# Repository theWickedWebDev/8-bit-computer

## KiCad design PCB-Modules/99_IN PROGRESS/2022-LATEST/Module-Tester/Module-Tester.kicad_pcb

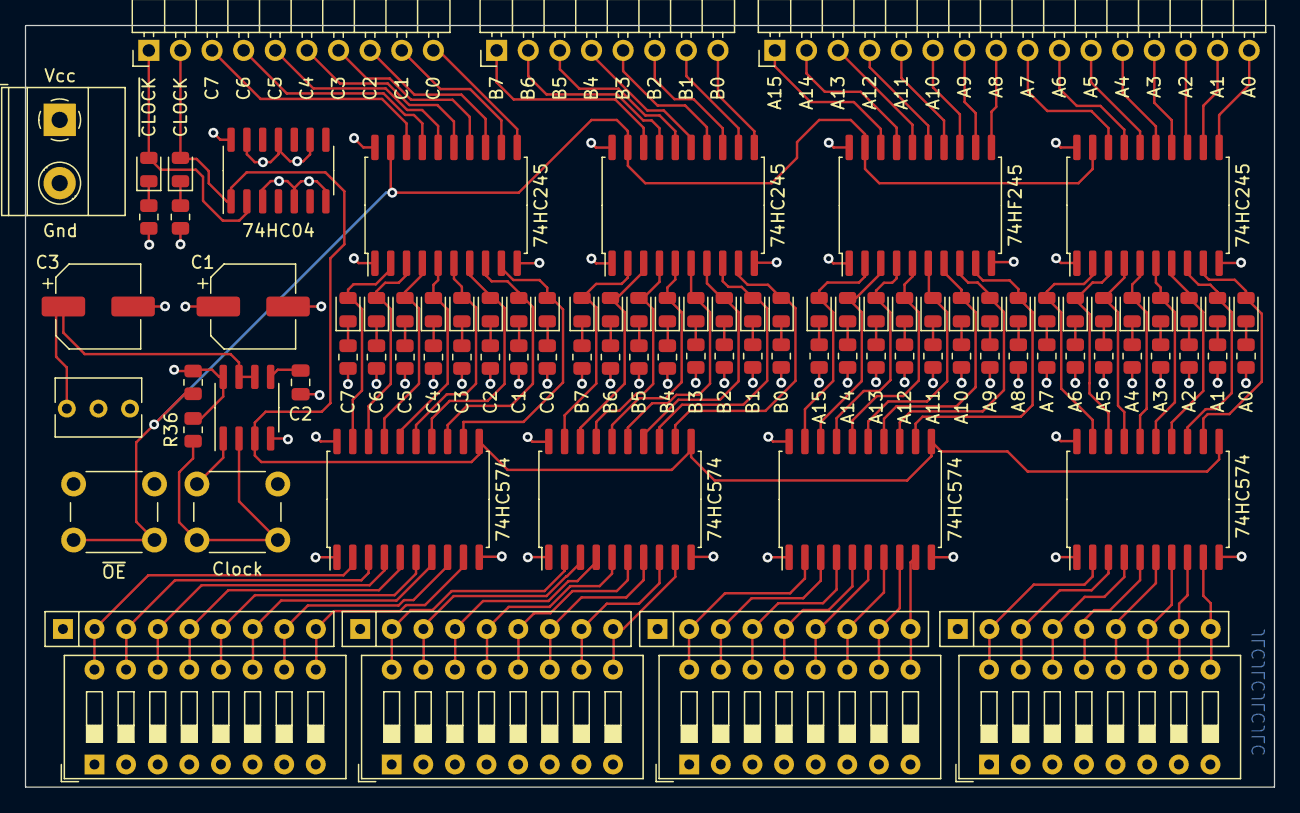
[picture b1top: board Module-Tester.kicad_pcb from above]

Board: 4 copper layers, 100.3 x 61.2 mm, 98 parts (0 on the bottom side), 138 nets.

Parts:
C1, C3: CS1V220M-CRE54; CP_Elec_6.3x5.4
C2: 0402B102K500NT; C_0805_2012Metric
D1, D2, D3, D4, D5, D6, D7, D8, D9, D10, D11, D12, D13, D14, D15, D16, D17, D18, D19, D20, D21, D22, D23, D24, D25, D26, D27, D28, D29, D30, D31, D32, D33, D34: LED; LED_0805_2012Metric
J1: Screw_Terminal_01x02; TerminalBlock_Phoenix_MKDS-1,5-2-5.08_1x02_P5.08mm_Horizont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
J2: Conn_01x10; PinHeader_1x10_P2.54mm_Horizontal
J3: Conn_01x08; PinHeader_1x08_P2.54mm_Horizontal
J4: Conn_01x16; PinHeader_1x16_P2.54mm_Horizontal
R1, R2, R3, R4, R5, R6, R7, R8, R9, R10, R11, R12, R13, R14, R15, R16, R17, R18, R19, R20, R21, R22, R23, R24, R25, R26, R27, R28, R29, R30, R31, R32, R33, R34: R_Small_US; R_0805_2012Metric
R35, R36: 0402WGF1002TCE; R_0805_2012Metric
RN1, RN2, RN3, RN4: R_Network08; R_Array_SIP9
RV1: 3296W-1-203; Potentiometer_Bourns_3266Y_Vertical
SW1, SW2, SW3, SW4: SW_DIP_x08; SW_DIP_SPSTx08_Slide_9.78x22.5mm_W7.62mm_P2.54mm
SW5: SW_SPST; SW_PUSH_6mm
SW6: sw-push; SW_PUSH_6mm
U1, U2, U5, U6: 74LS574; SOIC-20W_7.5x12.8mm_P1.27mm
U3, U4, U7, U8: 74LS245; SOIC-20W_7.5x12.8mm_P1.27mm
U9: LMC555CMX/NOPB; SOIC-8_3.9x4.9mm_P1.27mm
U10: 74LS04; SOIC-14_3.9x8.7mm_P1.27mm

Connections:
/R0: D10.2 (A), U1.12 (Q7), U3.9 (A7)
/R1: D9.2 (A), U1.13 (Q6), U3.8 (A6)
/R2: D8.2 (A), U1.14 (Q5), U3.7 (A5)
/R3: D7.2 (A), U1.15 (Q4), U3.6 (A4)
/R4: D6.2 (A), U1.16 (Q3), U3.5 (A3)
/R5: D5.2 (A), U1.17 (Q2), U3.4 (A2)
/R6: D4.2 (A), U1.18 (Q1), U3.3 (A1)
/R7: D3.2 (A), U1.19 (Q0), U3.2 (A0)
/R8: D18.2 (A), U2.12 (Q7), U4.9 (A7)
/R9: D17.2 (A), U2.13 (Q6), U4.8 (A6)
/R10: D16.2 (A), U2.14 (Q5), U4.7 (A5)
/R11: D15.2 (A), U2.15 (Q4), U4.6 (A4)
/R12: D14.2 (A), U2.16 (Q3), U4.5 (A3)
/R13: D13.2 (A), U2.17 (Q2), U4.4 (A2)
/R14: D12.2 (A), U2.18 (Q1), U4.3 (A1)
/R15: D11.2 (A), U2.19 (Q0), U4.2 (A0)
/R16: D34.2 (A), U5.12 (Q7), U7.9 (A7)
/R17: D33.2 (A), U5.13 (Q6), U7.8 (A6)
/R18: D32.2 (A), U5.14 (Q5), U7.7 (A5)
/R19: D31.2 (A), U5.15 (Q4), U7.6 (A4)
/R20: D30.2 (A), U5.16 (Q3), U7.5 (A3)
/R21: D29.2 (A), U5.17 (Q2), U7.4 (A2)
/R22: D28.2 (A), U5.18 (Q1), U7.3 (A1)
/R23: D27.2 (A), U5.19 (Q0), U7.2 (A0)
/R24: D26.2 (A), U6.12 (Q7), U8.9 (A7)
/R25: D25.2 (A), U6.13 (Q6), U8.8 (A6)
/R26: D24.2 (A), U6.14 (Q5), U8.7 (A5)
/R27: D23.2 (A), U6.15 (Q4), U8.6 (A4)
/R28: D22.2 (A), U6.16 (Q3), U8.5 (A3)
/R29: D21.2 (A), U6.17 (Q2), U8.4 (A2)
/R30: D20.2 (A), U6.18 (Q1), U8.3 (A1)
/R31: D19.2 (A), U6.19 (Q0), U8.2 (A0)
/S0: RN1.9 (R8), SW1.9, U1.9 (D7)
/S1: RN1.8 (R7), SW1.10, U1.8 (D6)
/S2: RN1.7 (R6), SW1.11, U1.7 (D5)
/S3: RN1.6 (R5), SW1.12, U1.6 (D4)
/S4: RN1.5 (R4), SW1.13, U1.5 (D3)
/S5: RN1.4 (R3), SW1.14, U1.4 (D2)
/S6: RN1.3 (R2), SW1.15, U1.3 (D1)
/S7: RN1.2 (R1), SW1.16, U1.2 (D0)
/S8: RN2.9 (R8), SW2.9, U2.9 (D7)
/S9: RN2.8 (R7), SW2.10, U2.8 (D6)
/S10: RN2.7 (R6), SW2.11, U2.7 (D5)
/S11: RN2.6 (R5), SW2.12, U2.6 (D4)
/S12: RN2.5 (R4), SW2.13, U2.5 (D3)
/S13: RN2.4 (R3), SW2.14, U2.4 (D2)
/S14: RN2.3 (R2), SW2.15, U2.3 (D1)
/S15: RN2.2 (R1), SW2.16, U2.2 (D0)
/S16: RN3.9 (R8), SW3.9, U5.9 (D7)
/S17: RN3.8 (R7), SW3.10, U5.8 (D6)
/S18: RN3.7 (R6), SW3.11, U5.7 (D5)
/S19: RN3.6 (R5), SW3.12, U5.6 (D4)
/S20: RN3.5 (R4), SW3.13, U5.5 (D3)
/S21: RN3.4 (R3), SW3.14, U5.4 (D2)
/S22: RN3.3 (R2), SW3.15, U5.3 (D1)
/S23: RN3.2 (R1), SW3.16, U5.2 (D0)
/S24: RN4.9 (R8), SW4.9, U6.9 (D7)
/S25: RN4.8 (R7), SW4.10, U6.8 (D6)
/S26: RN4.7 (R6), SW4.11, U6.7 (D5)
/S27: RN4.6 (R5), SW4.12, U6.6 (D4)
/S28: RN4.5 (R4), SW4.13, U6.5 (D3)
/S29: RN4.4 (R3), SW4.14, U6.4 (D2)
/S30: RN4.3 (R2), SW4.15, U6.3 (D1)
/S31: RN4.2 (R1), SW4.16, U6.2 (D0)
A0: J4.16, U7.11 (B7)
A1: J4.15, U7.12 (B6)
A2: J4.14, U7.13 (B5)
A3: J4.13, U7.14 (B4)
A4: J4.12, U7.15 (B3)
A5: J4.11, U7.16 (B2)
A6: J4.10, U7.17 (B1)
A7: J4.9, U7.18 (B0)
A8: J4.8, U8.11 (B7)
A9: J4.7, U8.12 (B6)
A10: J4.6, U8.13 (B5)
A11: J4.5, U8.14 (B4)
A12: J4.4, U8.15 (B3)
A13: J4.3, U8.16 (B2)
A14: J4.2, U8.17 (B1)
A15: J4.1, U8.18 (B0)
CLOCK: D2.2 (A), J2.2, U1.11 (Cp), U2.11 (Cp), U5.11 (Cp), U6.11 (Cp), U9.3 (Q), U10.1
CTL0: J2.10, U3.11 (B7)
CTL1: J2.9, U3.12 (B6)
CTL2: J2.8, U3.13 (B5)
CTL3: J2.7, U3.14 (B4)
CTL4: J2.6, U3.15 (B3)
CTL5: J2.5, U3.16 (B2)
CTL6: J2.4, U3.17 (B1)
CTL7: J2.3, U3.18 (B0)
D0: J3.8, U4.11 (B7)
D1: J3.7, U4.12 (B6)
D2: J3.6, U4.13 (B5)
D3: J3.5, U4.14 (B4)
D4: J3.4, U4.15 (B3)
D5: J3.3, U4.16 (B2)
D6: J3.2, U4.17 (B1)
D7: J3.1, U4.18 (B0)
GND: C1.2, C2.2, C3.2, J1.2, R1.2, R2.2, R3.2, R4.2, R5.2, R6.2, R7.2, R8.2, R9.2, R10.2, R11.2, R12.2, R13.2, R14.2, R15.2, R16.2, R17.2, R18.2, R19.2, R20.2, R21.2, R22.2, R23.2, R24.2, R25.2, R26.2, R27.2, R28.2, R29.2, R30.2, R31.2, R32.2, R33.2, R34.2, SW1.1, SW1.2, SW1.3, SW1.4, SW1.5, SW1.6, SW1.7, SW1.8, SW2.1, SW2.2, SW2.3, SW2.4, SW2.5, SW2.6, SW2.7, SW2.8, SW3.1, SW3.2, SW3.3, SW3.4, SW3.5, SW3.6, SW3.7, SW3.8, SW4.1, SW4.2, SW4.3, SW4.4, SW4.5, SW4.6, SW4.7, SW4.8, SW5.1 (A), SW6.1, U1.1 (OE), U1.10 (GND), U2.1 (OE), U2.10 (GND), U3.10 (GND), U4.10 (GND), U5.1 (OE), U5.10 (GND), U6.1 (OE), U6.10 (GND), U7.10 (GND), U8.10 (GND), U9.1 (GND), U10.3, U10.5, U10.7 (GND), U10.9, U10.11, U10.13
unnamed: C2.1, U9.5 (CV)
unnamed: D1.1 (K), R1.1
unnamed: D2.1 (K), R2.1
unnamed: D3.1 (K), R3.1
unnamed: D4.1 (K), R4.1
unnamed: D5.1 (K), R5.1
unnamed: D6.1 (K), R6.1
unnamed: D7.1 (K), R7.1
unnamed: D8.1 (K), R8.1
unnamed: D9.1 (K), R9.1
unnamed: D10.1 (K), R10.1
unnamed: D11.1 (K), R11.1
unnamed: D12.1 (K), R12.1
unnamed: D13.1 (K), R13.1
unnamed: D14.1 (K), R14.1
unnamed: D15.1 (K), R15.1
unnamed: D16.1 (K), R16.1
unnamed: D17.1 (K), R17.1
unnamed: D18.1 (K), R18.1
unnamed: D19.1 (K), R19.1
unnamed: D20.1 (K), R20.1
unnamed: D21.1 (K), R21.1
unnamed: D22.1 (K), R22.1
unnamed: D23.1 (K), R23.1
unnamed: D24.1 (K), R24.1
unnamed: D25.1 (K), R25.1
unnamed: D26.1 (K), R26.1
unnamed: D27.1 (K), R27.1
unnamed: D28.1 (K), R28.1
unnamed: D29.1 (K), R29.1
unnamed: D30.1 (K), R30.1
unnamed: D31.1 (K), R31.1
unnamed: D32.1 (K), R32.1
unnamed: D33.1 (K), R33.1
unnamed: D34.1 (K), R34.1
unnamed: R36.2, SW6.2, U9.2 (TR)
unnamed: C3.1, RV1.1, U9.6 (THR), U9.7 (DIS)
VCC: C1.1, J1.1, R35.2, R36.1, RN1.1 (common), RN2.1 (common), RN3.1 (common), RN4.1 (common), RV1.2, U1.20 (VCC), U2.20 (VCC), U3.1 (A->B), U3.20 (VCC), U4.1 (A->B), U4.20 (VCC), U5.20 (VCC), U6.20 (VCC), U7.1 (A->B), U7.20 (VCC), U8.1 (A->B), U8.20 (VCC), U9.4 (R), U9.8 (VCC), U10.14 (VCC)
~CLOCK: D1.2 (A), J2.1, U10.2
~OE: R35.1, SW5.2 (B), U3.19 (CE), U4.19 (CE), U7.19 (CE), U8.19 (CE)

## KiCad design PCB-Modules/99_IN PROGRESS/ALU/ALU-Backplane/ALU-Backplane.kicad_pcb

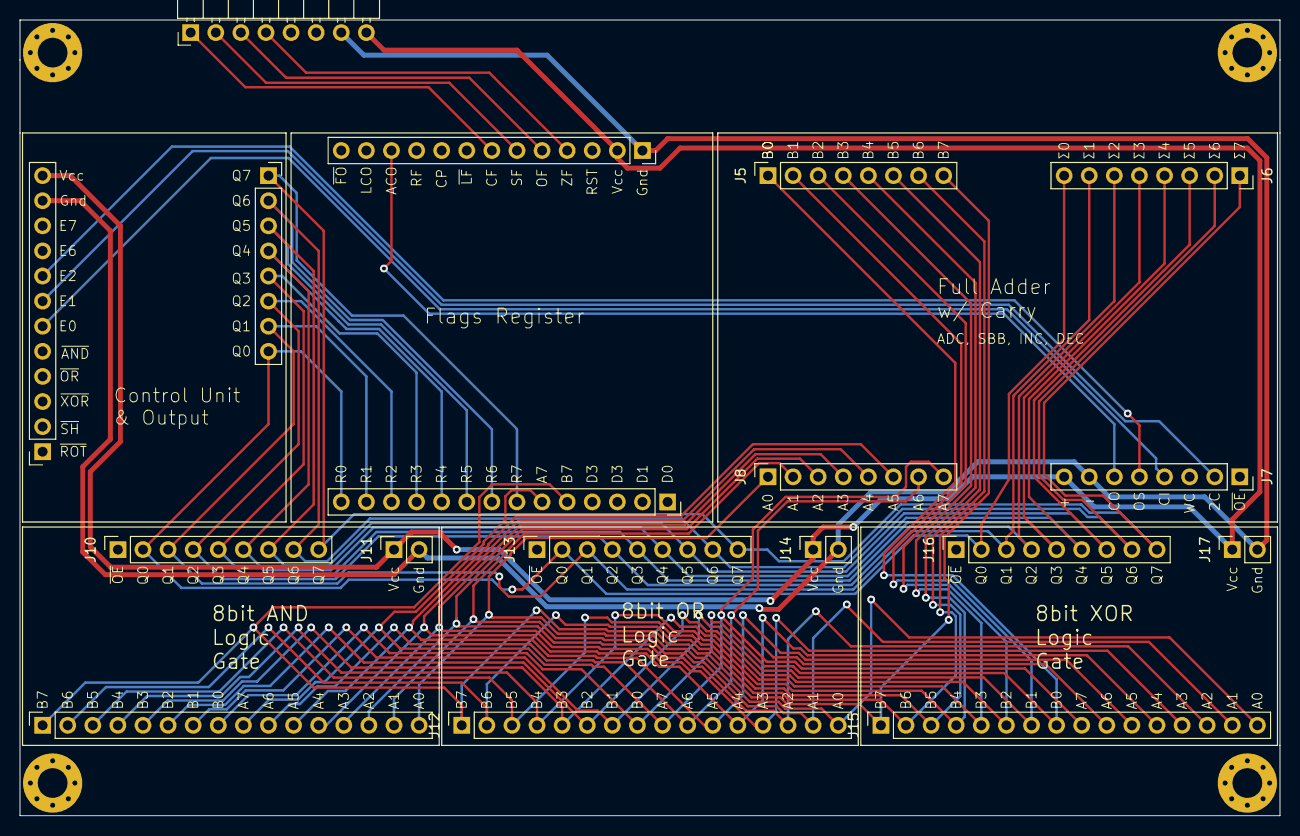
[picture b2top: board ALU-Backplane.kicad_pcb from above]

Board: 2 copper layers, 127.5 x 80.5 mm, 18 parts (0 on the bottom side), 34 nets.

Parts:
J1: Conn_01x12; PinSocket_1x12_P2.54mm_Vertical
J2, J5, J6, J7, J8: Conn_01x08; PinSocket_1x08_P2.54mm_Vertical
J3: Conn_01x13; PinSocket_1x13_P2.54mm_Vertical
J4: Conn_01x14; PinSocket_1x14_P2.54mm_Vertical
J9, J12, J15: Conn_01x16; PinSocket_1x16_P2.54mm_Vertical
J10, J13, J16: Conn_01x09; PinSocket_1x09_P2.54mm_Vertical
J11, J14, J17: Conn_01x02; PinSocket_1x02_P2.54mm_Vertical
J18: Conn_01x08; PinHeader_1x08_P2.54mm_Horizontal

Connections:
A0: J8.1, J9.16, J12.16, J15.16
A1: J8.2, J9.15, J12.15, J15.15
A2: J8.3, J9.14, J12.14, J15.14
A3: J8.4, J9.13, J12.13, J15.13
A4: J8.5, J9.12, J12.12, J15.12
A5: J8.6, J9.11, J12.11, J15.11
A6: J8.7, J9.10, J12.10, J15.10
A7: J4.6, J8.8, J9.9, J12.9, J15.9
ACO: J3.11, J7.6
B0: J5.1, J9.8, J12.8, J15.8
B1: J5.2, J9.7, J12.7, J15.7
B2: J5.3, J9.6, J12.6, J15.6
B3: J5.4, J9.5, J12.5, J15.5
B4: J5.5, J9.4, J12.4, J15.4
B5: J5.6, J9.3, J12.3, J15.3
B6: J5.7, J9.2, J12.2, J15.2
B7: J4.5, J5.8, J9.1, J12.1, J15.1
CF: J3.7, J18.1
E0: J1.6, J7.4
E1: J1.7, J7.2
E2: J1.8, J7.5
GND: J1.11, J3.1, J7.7, J11.2, J14.2, J17.2, J18.7
OF: J3.5, J18.3
Q0: J2.8, J4.14, J6.8, J10.2, J13.2, J16.2
Q1: J2.7, J4.13, J6.7, J10.3, J13.3, J16.3
Q2: J2.6, J4.12, J6.6, J10.4, J13.4, J16.4
Q3: J2.5, J4.11, J6.5, J10.5, J13.5, J16.5
Q4: J2.4, J4.10, J6.4, J10.6, J13.6, J16.6
Q5: J2.3, J4.9, J6.3, J10.7, J13.7, J16.7
Q6: J2.2, J4.8, J6.2, J10.8, J13.8, J16.8
Q7: J2.1, J4.7, J6.1, J10.9, J13.9, J16.9
SF: J3.6, J18.2
VCC: J1.12, J3.2, J7.8, J11.1, J14.1, J17.1, J18.8
ZF: J3.4, J18.4

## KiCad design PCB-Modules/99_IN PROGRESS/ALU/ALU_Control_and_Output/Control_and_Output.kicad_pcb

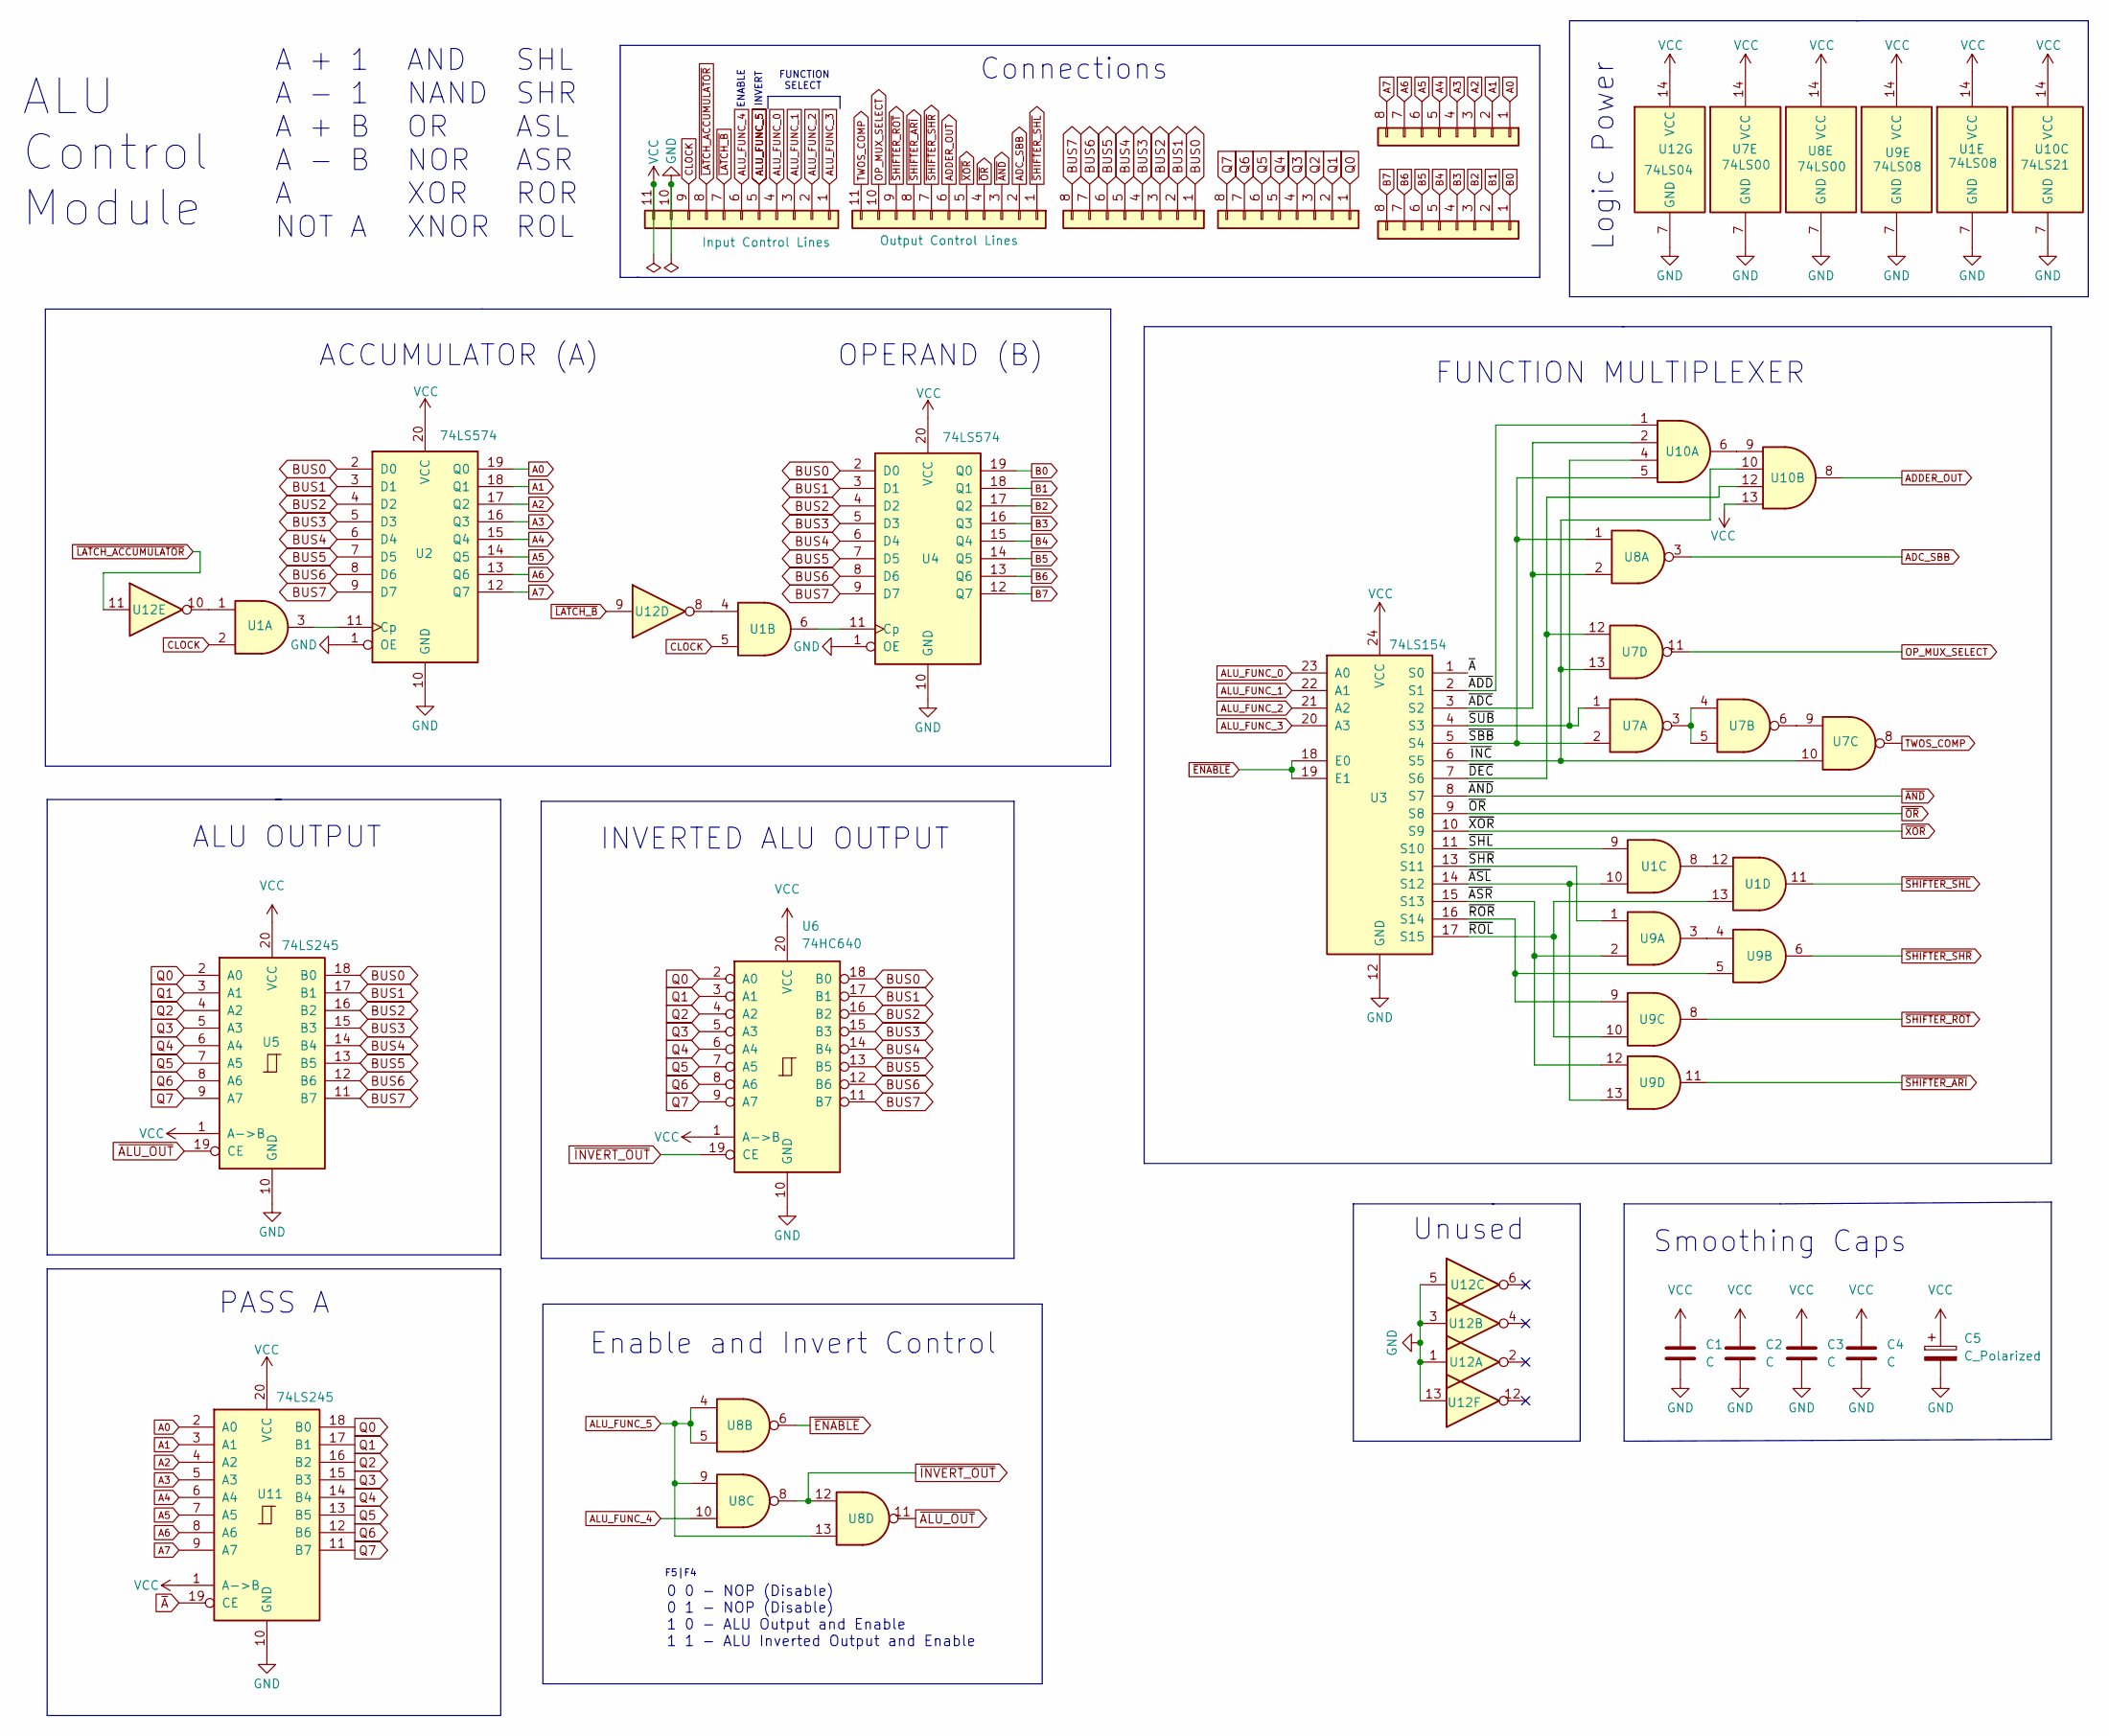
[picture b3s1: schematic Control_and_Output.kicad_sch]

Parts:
C1, C2, C3, C4: C; C_0805_2012Metric
C5: C_Polarized; CP_Elec_4x3
J1, J2, J4, J6: Conn_01x08; PinSocket_1x08_P2.54mm_Vertical
J3: Conn_01x11; PinHeader_1x11_P2.54mm_Vertical
J5: Conn_01x12; PinSocket_1x11_P2.54mm_Vertical
U1: 74LS08
U2, U4: 74LS574; SO-20_5.3x12.6mm_P1.27mm
U3: 74LS154; SOIC-24W_7.5x15.4mm_P1.27mm
U5, U11: 74LS245; TSSOP-20_4.4x6.5mm_P0.65mm
U6: 74HC640; SO-20_5.3x12.6mm_P1.27mm
U7: 74LS00; TSSOP-14_4.4x5mm_P0.65mm
U8: 74LS00
U9: 74LS08; TSSOP-14_4.4x5mm_P0.65mm
U10: 74LS21; SOIC-14_3.9x8.7mm_P1.27mm
U12: 74LS04

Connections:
/~ADC: U3.3 (S2), U8.2, U10.2
/~ADD: U3.2 (S1), U10.1
/~ASL: U1.10, U3.14 (S12), U9.13
/~ASR: U3.15 (S13), U9.2, U9.12
/~DEC: U3.7 (S6), U7.12, U10.12
/~INC: U3.6 (S5), U7.10, U7.13, U10.10
/~ROL: U1.13, U3.17 (S15), U9.10
/~ROR: U3.16 (S14), U9.5, U9.9
/~SBB: U3.5 (S4), U7.2, U8.1, U10.5
/~SHL: U1.9, U3.11 (S10)
/~SHR: U3.13 (S11), U9.1
/~SUB: U3.4 (S3), U7.1, U10.4
A0: J1.1, U2.19 (Q0), U11.2 (A0)
A1: J1.2, U2.18 (Q1), U11.3 (A1)
A2: J1.3, U2.17 (Q2), U11.4 (A2)
A3: J1.4, U2.16 (Q3), U11.5 (A3)
A4: J1.5, U2.15 (Q4), U11.6 (A4)
A5: J1.6, U2.14 (Q5), U11.7 (A5)
A6: J1.7, U2.13 (Q6), U11.8 (A6)
A7: J1.8, U2.12 (Q7), U11.9 (A7)
ADC_SBB: J3.2, U8.3
ADDER_OUT: J3.6, U10.8
ALU_FUNC_0: J5.4, U3.23 (A0)
ALU_FUNC_1: J5.3, U3.22 (A1)
ALU_FUNC_2: J5.2, U3.21 (A2)
ALU_FUNC_3: J5.1, U3.20 (A3)
ALU_FUNC_4: J5.6, U8.10
ALU_FUNC_5: J5.5, U8.4, U8.5, U8.9, U8.13
B0: J2.1, U4.19 (Q0)
B1: J2.2, U4.18 (Q1)
B2: J2.3, U4.17 (Q2)
B3: J2.4, U4.16 (Q3)
B4: J2.5, U4.15 (Q4)
B5: J2.6, U4.14 (Q5)
B6: J2.7, U4.13 (Q6)
B7: J2.8, U4.12 (Q7)
BUS0: J4.1, U2.2 (D0), U4.2 (D0), U5.18 (B0), U6.18 (B0)
BUS1: J4.2, U2.3 (D1), U4.3 (D1), U5.17 (B1), U6.17 (B1)
BUS2: J4.3, U2.4 (D2), U4.4 (D2), U5.16 (B2), U6.16 (B2)
BUS3: J4.4, U2.5 (D3), U4.5 (D3), U5.15 (B3), U6.15 (B3)
BUS4: J4.5, U2.6 (D4), U4.6 (D4), U5.14 (B4), U6.14 (B4)
BUS5: J4.6, U2.7 (D5), U4.7 (D5), U5.13 (B5), U6.13 (B5)
BUS6: J4.7, U2.8 (D6), U4.8 (D6), U5.12 (B6), U6.12 (B6)
BUS7: J4.8, U2.9 (D7), U4.9 (D7), U5.11 (B7), U6.11 (B7)
CLOCK: J5.9, U1.2, U1.5
GND: C1.2, C2.2, C3.2, C4.2, C5.2, J5.10, U1.7 (GND), U2.1 (OE), U2.10 (GND), U3.12 (GND), U4.1 (OE), U4.10 (GND), U5.10 (GND), U6.10 (GND), U7.7 (GND), U8.7 (GND), U9.7 (GND), U10.7 (GND), U11.10 (GND), U12.1, U12.3, U12.5, U12.7 (GND), U12.13
unnamed: U1.1, U12.10
unnamed: U1.3, U2.11 (Cp)
unnamed: U1.6, U4.11 (Cp)
unnamed: U1.8, U1.12
unnamed: U7.3, U7.4, U7.5
unnamed: U7.6, U7.9
unnamed: U9.3, U9.4
unnamed: U10.6, U10.9
unnamed: U1.4, U12.8
OP_MUX_SELECT: J3.10, U7.11
Q0: J6.1, U5.2 (A0), U6.2 (A0), U11.18 (B0)
Q1: J6.2, U5.3 (A1), U6.3 (A1), U11.17 (B1)
Q2: J6.3, U5.4 (A2), U6.4 (A2), U11.16 (B2)
Q3: J6.4, U5.5 (A3), U6.5 (A3), U11.15 (B3)
Q4: J6.5, U5.6 (A4), U6.6 (A4), U11.14 (B4)
Q5: J6.6, U5.7 (A5), U6.7 (A5), U11.13 (B5)
Q6: J6.7, U5.8 (A6), U6.8 (A6), U11.12 (B6)
Q7: J6.8, U5.9 (A7), U6.9 (A7), U11.11 (B7)
TWOS_COMP: J3.11, U7.8
VCC: C1.1, C2.1, C3.1, C4.1, C5.1, J5.11, U1.14 (VCC), U2.20 (VCC), U3.24 (VCC), U4.20 (VCC), U5.1 (A->B), U5.20 (VCC), U6.1 (A->B), U6.20 (VCC), U7.14 (VCC), U8.14 (VCC), U9.14 (VCC), U10.13, U10.14 (VCC), U11.1 (A->B), U11.20 (VCC), U12.14 (VCC)
~ALU_OUT: U5.19 (CE), U8.11
~AND: J3.3, U3.8 (S7)
~A: U3.1 (S0), U11.19 (CE)
~ENABLE: U3.18 (E0), U3.19 (E1), U8.6
~INVERT_OUT: U6.19 (CE), U8.8, U8.12
~LATCH_ACCUMULATOR: J5.8, U12.11
~LATCH_B: J5.7, U12.9
~OR: J3.4, U3.9 (S8)
~SHIFTER_ARI: J3.8, U9.11
~SHIFTER_ROT: J3.9, U9.8
~SHIFTER_SHL: J3.1, U1.11
~SHIFTER_SHR: J3.7, U9.6
~XOR: J3.5, U3.10 (S9)

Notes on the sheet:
Connections
INVERTED ALU OUTPUT
AND NAND OR NOR XOR XNOR
ALU Control Module
Unused
ALU OUTPUT
OPERAND (B)
PASS A
Logic Power
0 0 - NOP (Disable) 0 1 - NOP (Disable) 1 0 - ALU Output and Enable 1 1 - ALU Inverted Output and Enable
ENABLE
Enable and Invert Control
FUNCTION SELECT
F5|F4
INVERT
SHL SHR ASL ASR ROR ROL
FUNCTION MULTIPLEXER
A + 1 A - 1 A + B A - B A NOT A
ACCUMULATOR (A)
Smoothing Caps

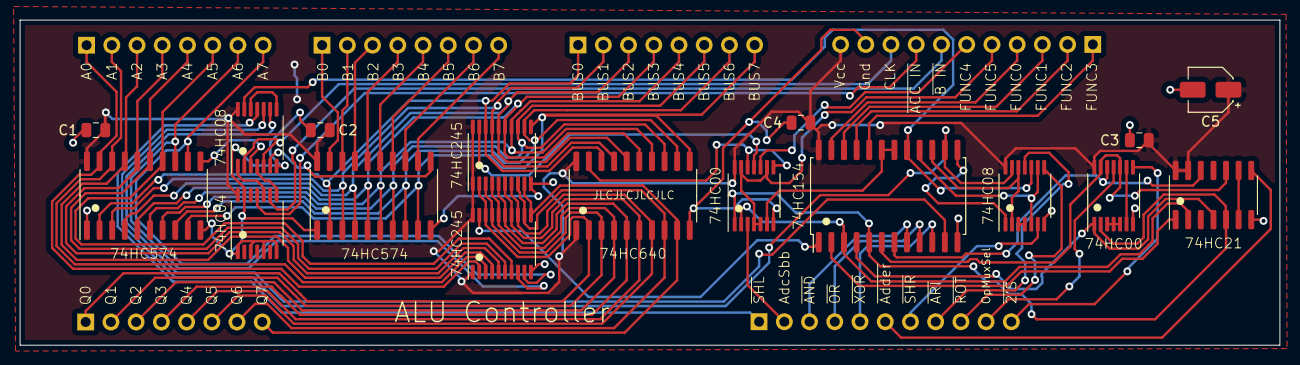
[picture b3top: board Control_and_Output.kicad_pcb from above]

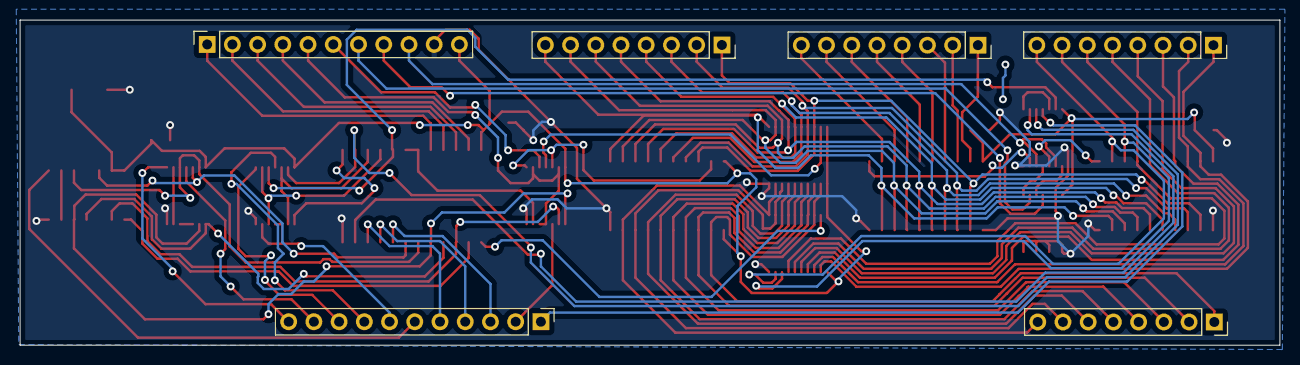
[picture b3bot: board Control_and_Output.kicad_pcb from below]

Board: 2 copper layers, 126.9 x 32.7 mm, 23 parts (6 on the bottom side), 79 nets.

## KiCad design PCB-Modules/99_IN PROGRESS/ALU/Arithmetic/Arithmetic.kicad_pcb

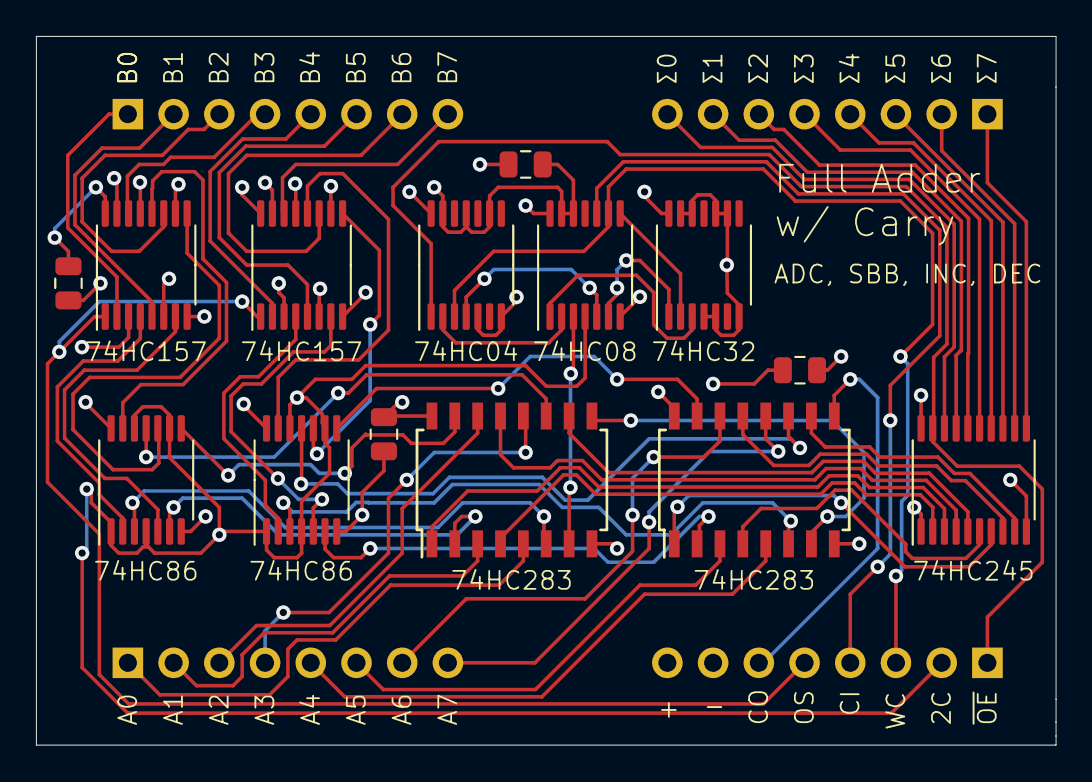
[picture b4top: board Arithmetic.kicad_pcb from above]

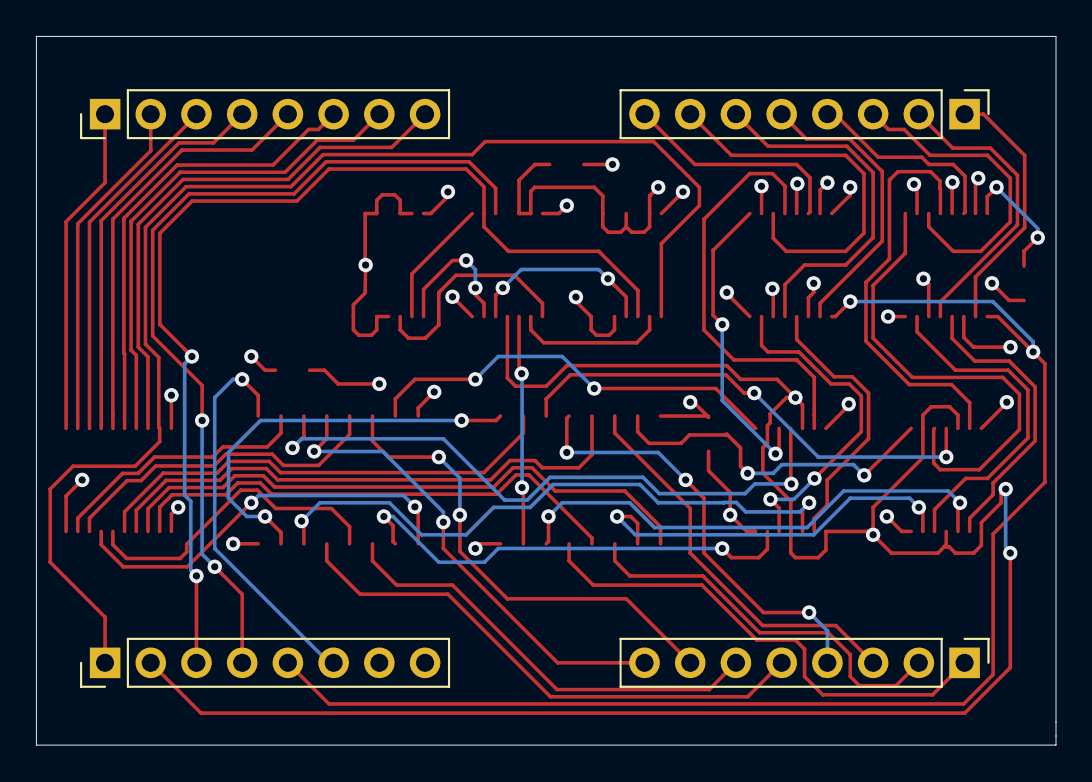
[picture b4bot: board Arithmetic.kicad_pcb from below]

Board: 4 copper layers, 56.6 x 39.4 mm, 18 parts (4 on the bottom side), 63 nets.

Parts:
C1, C2, C3, C4: C; C_0805_2012Metric
J1, J2, J3, J4: Conn_01x08; PinHeader_1x08_P2.54mm_Vertical
U1, U2: 74LS157; TSSOP-16_4.4x5mm_P0.65mm
U3, U4: 74LS86; TSSOP-14_4.4x5mm_P0.65mm
U5, U6: 74LS283; SOIC-16W_5.3x10.2mm_P1.27mm
U7: 74LS245; TSSOP-20_4.4x6.5mm_P0.65mm
U32: 74LS04; TSSOP-14_4.4x5mm_P0.65mm
U33: 74LS08; TSSOP-14_4.4x5mm_P0.65mm
U34: 74LS32; TSSOP-14_4.4x5mm_P0.65mm

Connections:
A0: J1.1, U5.5
A1: J1.2, U5.3
A2: J1.3, U5.14
A3: J1.4, U5.12
A4: J1.5, U6.5
A5: J1.6, U6.3
A6: J1.7, U6.14
A7: J1.8, U6.12
ADC_SBB: J4.3, U32.3, U33.9
ADDER_CARRY_IN: U5.7, U33.3
ADDER_CARRY_OUT: J4.6, U6.9
B0: J2.1, U1.2
B1: J2.2, U1.5
B2: J2.3, U1.11
B3: J2.4, U1.14
B4: J2.5, U2.2
B5: J2.6, U2.5
B6: J2.7, U2.11
B7: J2.8, U2.14
CARRY_FLAG_IN: J4.4, U33.10
GND: C1.2, C2.2, C3.2, C4.2, J4.7, U1.8, U1.15, U2.8, U2.15, U3.7, U4.7, U5.8, U6.8, U7.10, U32.5, U32.7, U32.9, U32.11, U32.13, U33.7, U33.12, U33.13, U34.4, U34.5, U34.7, U34.9, U34.10, U34.12, U34.13
unnamed: U1.4, U3.2
unnamed: U1.7, U3.5
unnamed: U1.9, U3.10
unnamed: U1.12, U3.13
unnamed: U2.4, U4.2
unnamed: U2.7, U4.5
unnamed: U2.9, U4.10
unnamed: U2.12, U4.13
unnamed: U5.1, U7.3
unnamed: U5.4, U7.2
unnamed: U5.9, U6.7
unnamed: U5.10, U7.5
unnamed: U5.13, U7.4
unnamed: U6.1, U7.7
unnamed: U6.4, U7.6
unnamed: U6.10, U7.9
unnamed: U6.13, U7.8
unnamed: U32.2, U33.2
unnamed: U32.4, U33.5
unnamed: U33.1, U34.3
unnamed: U33.6, U34.1
unnamed: U33.8, U34.2
OP0: U3.3, U5.6
OP1: U3.6, U5.2
OP2: U3.8, U5.15
OP3: U3.11, U5.11
OP4: U4.3, U6.6
OP5: U4.6, U6.2
OP6: U4.8, U6.15
OP7: U4.11, U6.11
OP_MUX_SEL: J4.5, U1.1, U2.1
SUM0: J3.8, U7.18
SUM1: J3.7, U7.17
SUM2: J3.6, U7.16
SUM3: J3.5, U7.15
SUM4: J3.4, U7.14
SUM5: J3.3, U7.13
SUM6: J3.2, U7.12
SUM7: J3.1, U7.11
TWOS_COMP: J4.2, U3.1, U3.4, U3.9, U3.12, U4.1, U4.4, U4.9, U4.12, U33.4
VCC: C1.1, C2.1, C3.1, C4.1, J4.8, U1.3, U1.6, U1.10, U1.13, U1.16, U2.3, U2.6, U2.10, U2.13, U2.16, U3.14, U4.14, U5.16, U6.16, U7.1, U7.20, U32.14, U33.14, U34.14
~ADDER_OUT: J4.1, U7.19, U32.1

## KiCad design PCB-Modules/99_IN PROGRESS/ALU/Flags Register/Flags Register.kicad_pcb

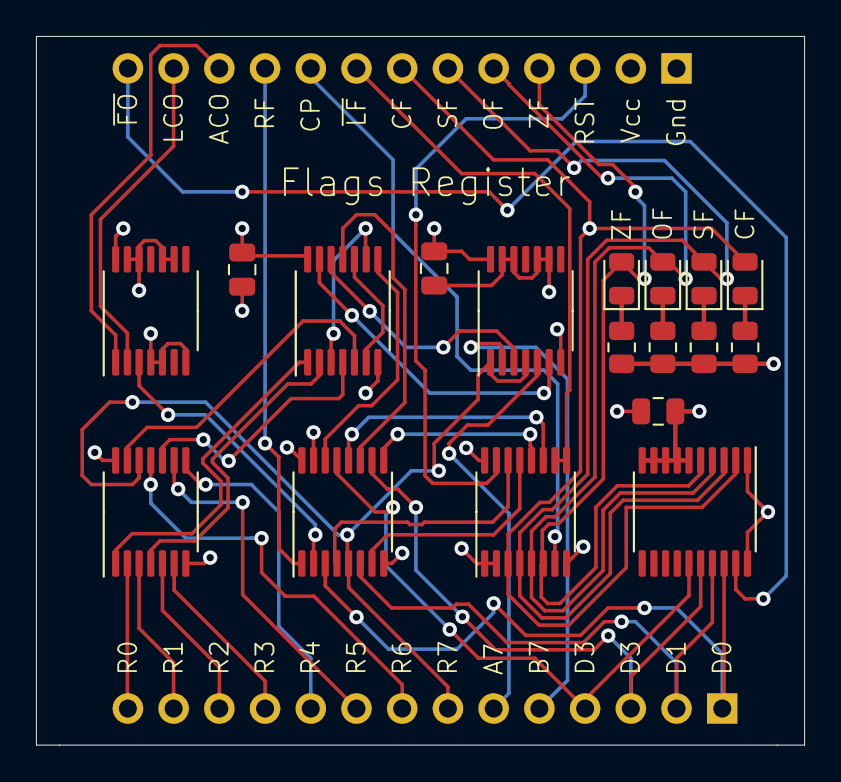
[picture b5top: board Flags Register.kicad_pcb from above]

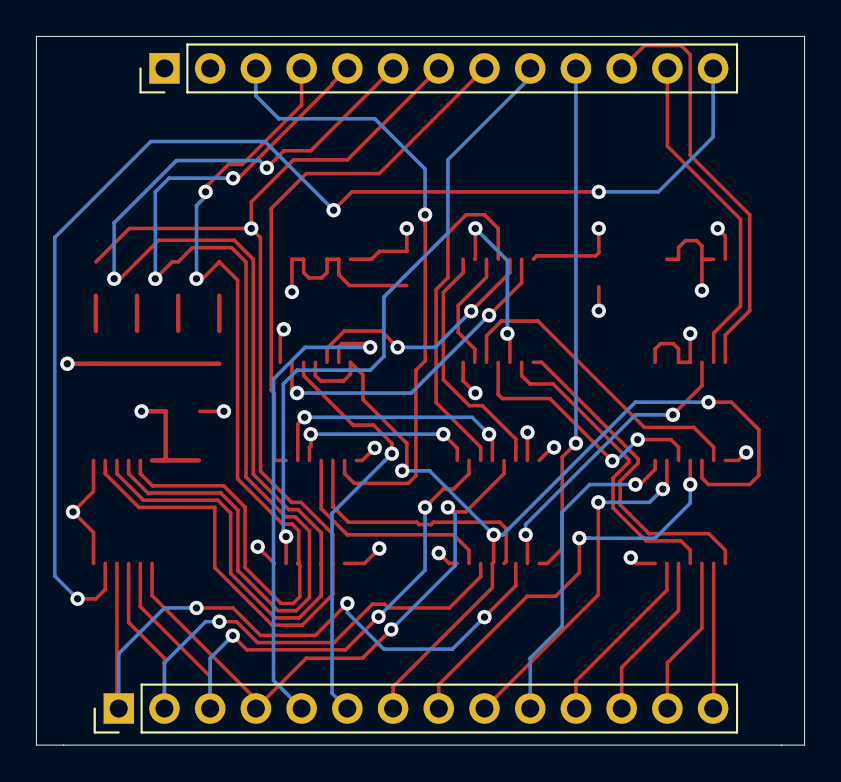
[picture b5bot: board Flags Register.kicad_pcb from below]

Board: 4 copper layers, 42.7 x 39.4 mm, 20 parts (2 on the bottom side), 46 nets.

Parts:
C1, C2, C3: C; C_0805_2012Metric
D1, D2, D3, D4: LED; LED_0805_2012Metric
J1: Conn_01x13; PinHeader_1x13_P2.54mm_Vertical
J2: Conn_01x14; PinHeader_1x14_P2.54mm_Vertical
R1, R2, R3, R4: R_US; R_0805_2012Metric
U1: 74LS173; TSSOP-16_4.4x5mm_P0.65mm
U2: 74LS245; TSSOP-20_4.4x6.5mm_P0.65mm
U35: 74LS32; TSSOP-14_4.4x5mm_P0.65mm
U36: 74LS02; TSSOP-14_4.4x5mm_P0.65mm
U37: 74LS08; TSSOP-14_4.4x5mm_P0.65mm
U38: 74LS157; TSSOP-16_4.4x5mm_P0.65mm
U39: 74LS86; TSSOP-14_4.4x5mm_P0.65mm

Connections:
A7: J2.6, U39.5
ARITHMETIC_CARRY_OUT: J1.11, U35.1
B7: J2.5, U39.2
BUS0: J2.1, U2.18 (B0), U38.3 (I1a)
BUS1: J2.2, U2.17 (B1), U38.6 (I1b)
BUS2: J2.3, U2.16 (B2), U38.10 (I1c)
BUS3: J2.4, U2.15 (B3), U38.13 (I1d)
CF: D1.2 (A), J1.7, U1.3 (Q0), U2.2 (A0)
CLOCK: J1.9, U1.7 (Cp)
GND: C1.2, C2.2, C3.2, J1.1, R1.2, R2.2, R3.2, R4.2, U1.1 (Oe1), U1.2 (Oe2), U1.8 (GND), U2.6 (A4), U2.7 (A5), U2.8 (A6), U2.9 (A7), U2.10 (GND), U35.4, U35.5, U35.7 (GND), U35.9, U35.10, U35.12, U35.13, U36.7 (GND), U37.7 (GND), U38.8 (GND), U38.15 (E), U39.7 (GND), U39.9, U39.10, U39.12, U39.13
LOGICAL_CARRY_OUT: J1.12, U35.2
MUX_CARRY: U1.14 (D0), U38.4 (Za)
MUX_OVERFLOW: U1.12 (D2), U38.9 (Zc)
MUX_SIGN: U1.13 (D1), U38.7 (Zb)
MUX_ZERO: U1.11 (D3), U38.12 (Zd)
unnamed: D1.1 (K), R1.1
unnamed: D2.1 (K), R2.1
unnamed: D3.1 (K), R3.1
unnamed: D4.1 (K), R4.1
unnamed: U35.3, U38.2 (I0a)
unnamed: U36.1, U37.1
unnamed: U36.4, U37.2
unnamed: U36.10, U37.4
unnamed: U36.13, U37.5
unnamed: U37.3, U37.9
unnamed: U37.6, U37.10
unnamed: U37.12, U39.3
unnamed: U37.13, U39.6
OF: D3.2 (A), J1.5, U1.5 (Q2), U2.4 (A2)
OVERFLOW: U37.11, U38.11 (I0c)
RES0: J2.14, U36.2
RES1: J2.13, U36.3
RES2: J2.12, U36.5
RES3: J2.11, U36.6
RES4: J2.10, U36.8
RES5: J2.9, U36.9
RES6: J2.8, U36.11
RES7: J2.7, U36.12, U38.5 (I0b), U39.1, U39.4
RESET: J1.3, U1.15 (Mr)
RESTORE_FLAGS: J1.10, U38.1 (S)
SF: D2.2 (A), J1.6, U1.4 (Q1), U2.3 (A1)
VCC: C1.1, C2.1, C3.1, J1.2, U1.16 (VCC), U2.1 (A->B), U2.20 (VCC), U35.14 (VCC), U36.14 (VCC), U37.14 (VCC), U38.16 (VCC), U39.14 (VCC)
ZERO: U37.8, U38.14 (I0d)
ZF: D4.2 (A), J1.4, U1.6 (Q3), U2.5 (A3)
~FLAG_OUT: J1.13, U2.19 (CE)
~LATCH_FLAGS: J1.8, U1.9 (E1), U1.10 (E2)
